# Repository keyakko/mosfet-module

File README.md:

# mosfet-module
Re-purposing a motherboard MOSFET to serve as an electrical switch.

## NOTE
I am a beginner in circuit design, so there may be issues with the wiring.

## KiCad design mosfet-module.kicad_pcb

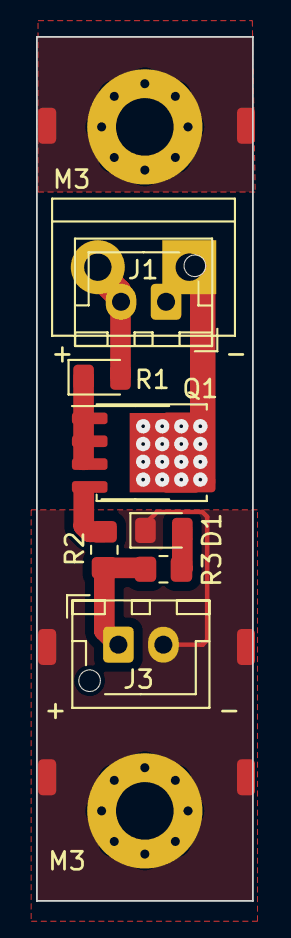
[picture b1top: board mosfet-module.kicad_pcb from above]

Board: 2 copper layers, 12.0 x 48.0 mm, 11 parts (0 on the bottom side), 7 nets.

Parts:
D1: LED; LED_0805_2012Metric_Pad1.15x1.40mm_HandSolder
J1: Terminal; TerminalBlock_bornier-2_P5.08mm
J2, J3: Conn_01x02_Socket; JST_XH_B2B-XH-AM_1x02_P2.50mm_Vertical
M3, M3#2: MountingHole_3.2mm_M3_Pad_Via
Q1: CSD17578Q5A; TDSON-8-1
Q2: CSD17578Q5A; SOP-8_3.76x4.96mm_P1.27mm
R1: R; LED_0805_2012Metric_Pad1.15x1.40mm_HandSolder
R2, R3: R; R_0805_2012Metric_Pad1.20x1.40mm_HandSolder

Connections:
GND: D1.1 (K), J3.2, M3.1, M3#2.1
unnamed: D1.2 (A), R3.2
unnamed: J1.1, J2.1, Q1.5 (D), Q2.5 (D), Q2.6, Q2.7, Q2.8
unnamed: J1.2, J2.2, R1.2
unnamed: J3.1, R2.2, R3.1
unnamed: Q1.4 (G), Q2.4 (G), R2.1
unnamed: Q1.1 (S), Q1.2 (S), Q1.3 (S), Q2.1 (S), Q2.2 (S), Q2.3 (S), R1.1

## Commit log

2023-09-03 add `.gitignore`
2023-09-03 add main PCB project
2023-09-03 add panelized PCB project files
2023-09-03 add `README.md`
2023-09-03 fix typo
2023-09-04 update main PCB
2023-09-04 update panelized PCB
2023-09-04 update an image in README
2023-09-04 update main PCB project files
2023-09-04 update an panelize configuration for kikit
